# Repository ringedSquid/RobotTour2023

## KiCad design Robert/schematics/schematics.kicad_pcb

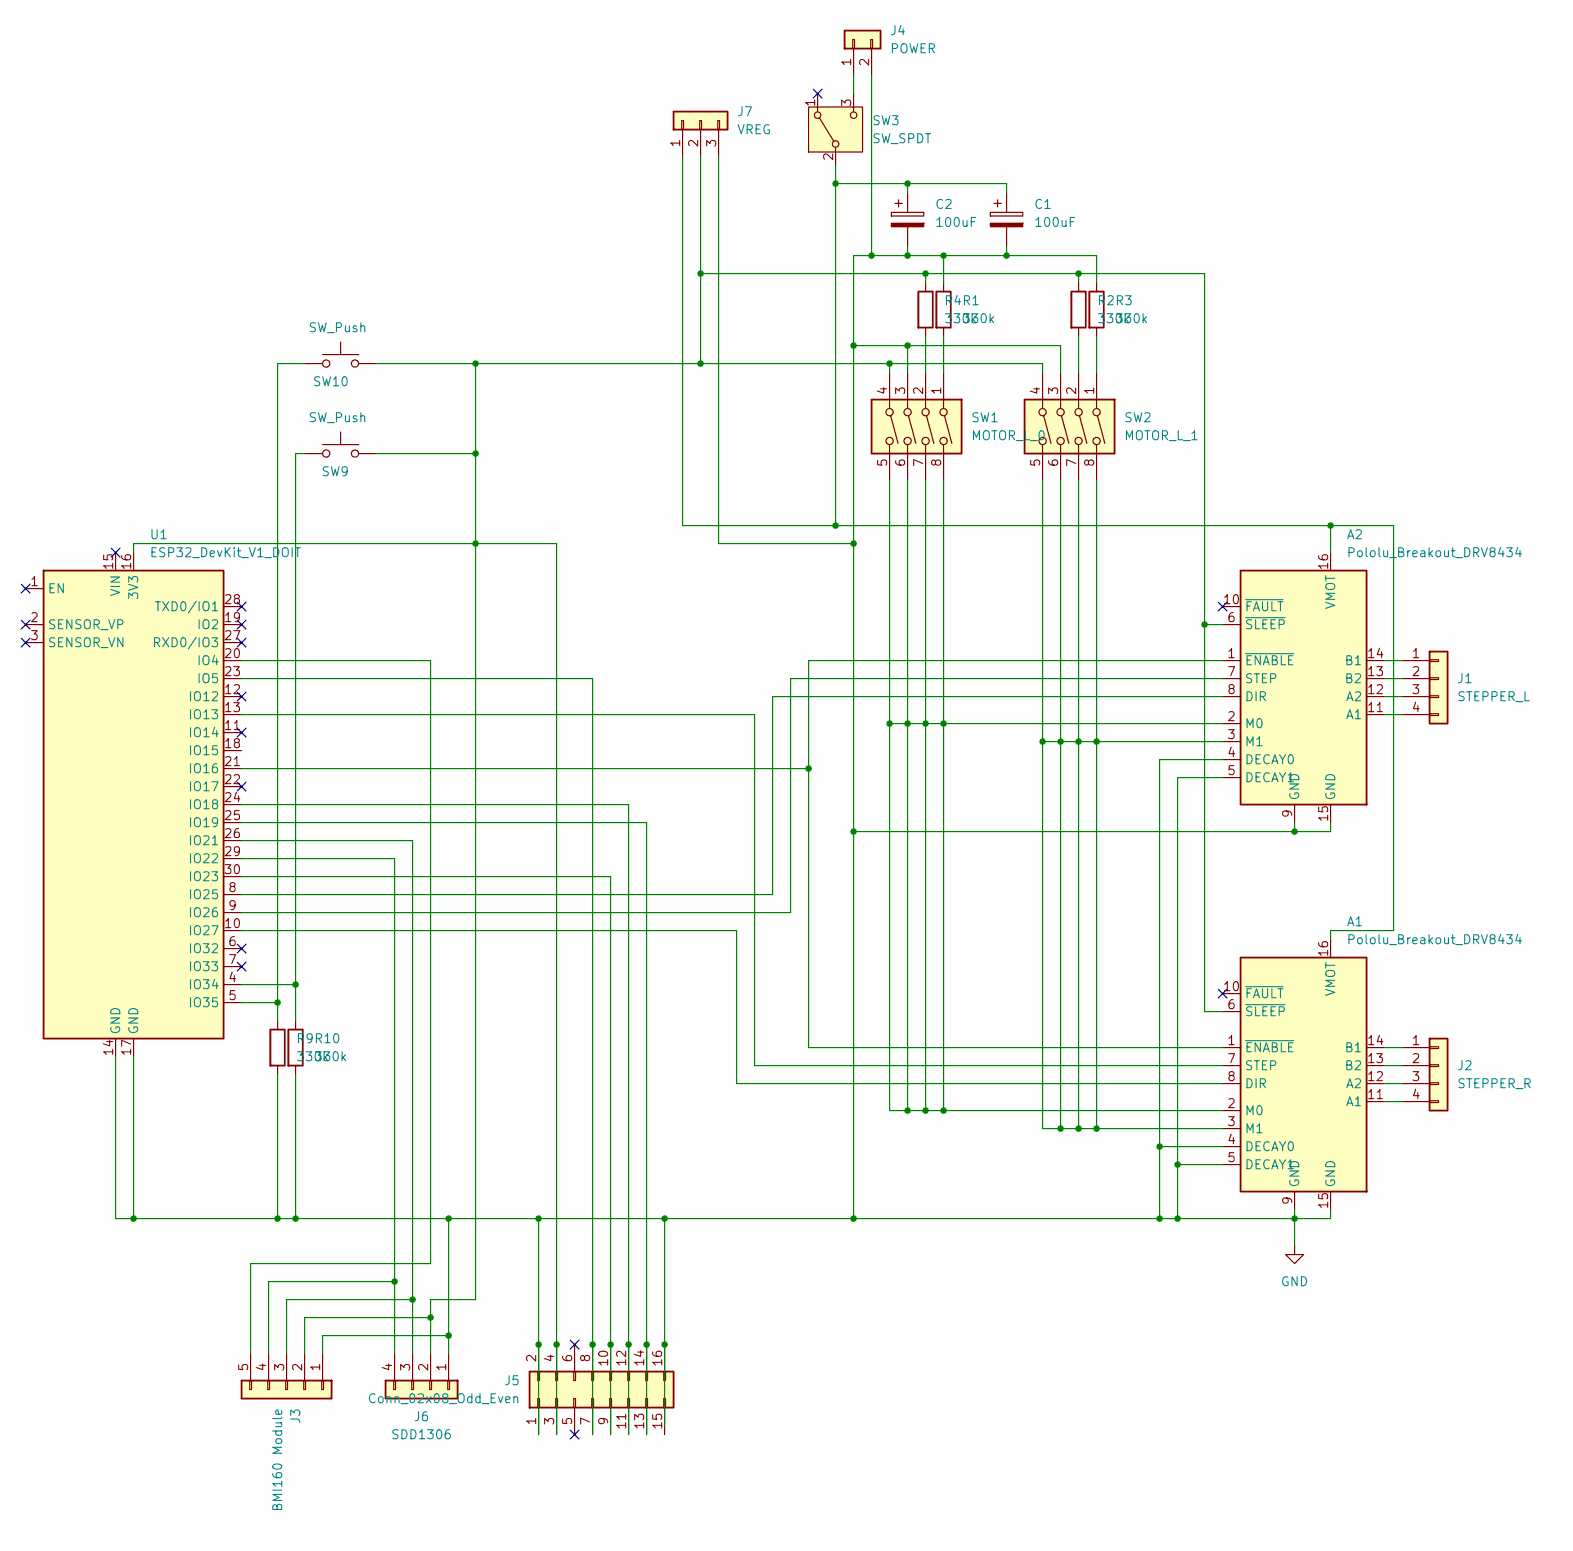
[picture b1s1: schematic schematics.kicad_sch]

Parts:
A1, A2: Pololu_Breakout_DRV8434; Pololu_Breakout-16_15.2x20.3mm
C1, C2: 100uF; CP_Radial_Tantal_D6.0mm_P2.50mm
J1: STEPPER_L; JST_PH_B4B-PH-K_1x04_P2.00mm_Vertical
J2: STEPPER_R; JST_PH_B4B-PH-K_1x04_P2.00mm_Vertical
J3: BMI160 Module; JST_PH_B5B-PH-K_1x05_P2.00mm_Vertical
J4: POWER; JST_PH_B2B-PH-K_1x02_P2.00mm_Vertical
J5: Conn_02x08_Odd_Even; PinHeader_2x08_P2.54mm_Vertical
J6: SDD1306; PinHeader_1x04_P2.54mm_Vertical
J7: VREG; PinHeader_1x03_P2.00mm_Vertical
R1, R2, R3, R4, R9, R10: 330k; R_Axial_DIN0207_L6.3mm_D2.5mm_P2.54mm_Vertical
SW1: MOTOR_L_0; SW_DIP_SPSTx04_Slide_9.78x12.34mm_W7.62mm_P2.54mm
SW2: MOTOR_L_1; SW_DIP_SPSTx04_Slide_9.78x12.34mm_W7.62mm_P2.54mm
SW3: SW_SPDT; SW_Toggle_Blue_wSlots
SW9, SW10: SW_Push; SW_PUSH_6mm_H5mm
U1: ESP32_DevKit_V1_DOIT; esp32_devkit_v1_doit

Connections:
GND: A1.4 (DECAY0), A1.5 (DECAY1), A1.9 (GND), A1.15 (GND), A2.4 (DECAY0), A2.5 (DECAY1), A2.9 (GND), A2.15 (GND), C1.2, C2.2, J3.1, J4.2, J5.1, J5.2, J5.16, J6.1, J7.3, R1.1, R3.1, R9.2, R10.2, SW1.3, SW2.3, U1.14 (GND), U1.17 (GND)
unnamed: A1.11 (A1), J2.4
unnamed: A1.12 (A2), J2.3
unnamed: A1.14 (B1), J2.1
unnamed: A1.13 (B2), J2.2
unnamed: A1.8 (DIR), U1.10 (IO27)
unnamed: A1.2 (M0), A2.2 (M0), SW1.5, SW1.6, SW1.7, SW1.8
unnamed: A1.3 (M1), A2.3 (M1), SW2.5, SW2.6, SW2.7, SW2.8
unnamed: A1.7 (STEP), U1.13 (IO13)
unnamed: A1.16 (VMOT), A2.16 (VMOT), C1.1, C2.1, J7.1, SW3.2 (B)
unnamed: A1.1 (~ENABLE), A2.1 (~ENABLE), U1.21 (IO16)
unnamed: A1.6 (~SLEEP), A2.6 (~SLEEP), J3.2, J5.3, J5.4, J6.2, J7.2, R2.1, R4.1, SW1.4, SW2.4, SW9.2, SW10.2, U1.16 (3V3)
unnamed: A2.11 (A1), J1.4
unnamed: A2.12 (A2), J1.3
unnamed: A2.14 (B1), J1.1
unnamed: A2.13 (B2), J1.2
unnamed: A2.8 (DIR), U1.8 (IO25)
unnamed: A2.7 (STEP), U1.9 (IO26)
unnamed: J3.3, J6.3, U1.26 (IO21)
unnamed: J3.4, J6.4, U1.29 (IO22)
unnamed: J3.5, U1.20 (IO4)
unnamed: J4.1, SW3.3 (C)
unnamed: J5.7, J5.8, U1.23 (IO5)
unnamed: J5.9, J5.10, U1.30 (IO23)
unnamed: J5.11, J5.12, U1.24 (IO18)
unnamed: J5.13, J5.14, U1.25 (IO19)
unnamed: R1.2, SW1.1
unnamed: R2.2, SW2.2
unnamed: R3.2, SW2.1
unnamed: R4.2, SW1.2
unnamed: R10.1, SW9.1, U1.4 (IO34)
unnamed: R9.1, SW10.1, U1.5 (IO35)

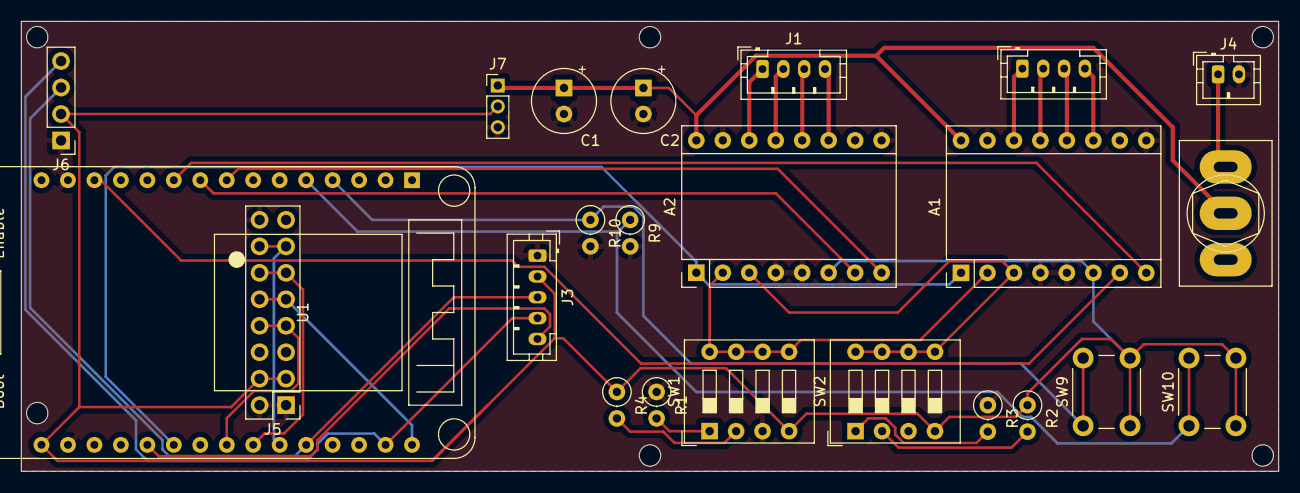
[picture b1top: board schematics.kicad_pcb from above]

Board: 2 copper layers, 120.7 x 43.2 mm, 23 parts (0 on the bottom side), 32 nets.

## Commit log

2018-07-24 states!'
2023-10-26 stuff
2023-11-01 switched over to circuitpython
2023-11-06 KINEMATICS!
2023-11-08 objects
2023-11-08 e e e e o o o o
2023-11-09 odometry class finished, some conversions are straighup wrong
2023-11-12 pure pursuit done
2023-11-16 DonE
2023-11-29 fixed crashes
2023-11-30 started theta PID
2023-12-01 I realize the theta!
2023-12-04 partially pid for heading
2023-12-05 fixed turning!
2023-12-12 dwada
2023-12-13 LEBRON!
2024-01-02 SimplePursuit started
2024-01-05 SimplePursuit started, errors bound
2024-01-08 Robot class started, rdist, rtime calculations needed
2024-01-09 Robot class finished, sorting out some errors
2024-01-11 Pathfinding works! (sort of), speed calculations and stop conditon are broken
2024-01-13 USE IMU, FIX TIMING ISSUE< ODO DRIFT, OVERTURN
2024-01-16 fixed timing, tuned pids
2024-01-17 WORKS FOR MIT, IMU PLZ?
2024-01-18 final for mit
2024-01-24 new file structure
2024-01-30 Robert's motion profile complete!
2024-01-31 calibration
2024-01-31 started control logic, needs imu code for heading + SD card reading + display
2024-01-31 path following done
2024-01-31 started gyro, i2c doesnt work!
2024-02-01 IMU bugs worked out, started file read, get turns done
2024-02-01 FSM for main loop started, SD reading finished, needs testing
2024-02-01 Clinton update
2024-02-01 gyro works
2024-02-02 night before regionals, test SD reading and paths
2024-02-02 fixed clinton edges
2024-02-03 regionals
2024-02-04 regionals push
2024-02-05 dual core Bruh
2024-02-06 dual core fixes, increase watchdog timer
2024-02-06 turns dont wokr ;(
2024-02-07 BROWN
2024-02-08 BROWN v2
2024-02-08 dual kind of works, turns inconcistent
2024-02-08 dual core inconsistent
2024-02-09 dual core stuff
2024-02-09 pray and pray for brown
2024-02-09 brown team b
2024-02-09 praying didnt work, god isnt real
2024-02-09 poop
2024-02-09 POOPY
2024-02-10 cool
2024-02-10 brownish
2024-02-19 new schematics
2024-02-20 pcb?
2024-02-22 pcb done, double check needed
2024-02-23 revised pcb
2024-02-29 is a gate method, reading in gates
2024-02-29 new turns!
2024-02-29 fixing sideways drift
2024-03-08 x-offset!
2024-03-09 fixed 180s
2024-03-11 offets work
